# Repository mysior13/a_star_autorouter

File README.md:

Algorytm trasowania ścieżek na podstawie elementów rozmieszczonych na płytce oraz logicznych połączeń między tymi elementami, 
wyznacza możliwie najkrótsze ścieżki. 
Cechy programu:
-algorytm zalicza się do grupy algorytmów rastrowych,
-wyszukiwanie najkrótszej ścieżki przeprowadzane jest wykorzystaniem algorytmu A*,
-dane wejściowe (schemat płytki z rozłożonymi elementami oraz logicznymi połączeniami między nimi) wczytywane są z programu KiCad(program do projektowania płytek obwodów drukowanych)
-użytkownik posiada możliwość ustalenia maksymalnej liczby przelotek między warstwami, jakie dodać może algorytm,
-na wyjściu algorytm generuje obrazy z wyznaczonymi obszarami miedzi na każdej warstwie płytki drukowanej.

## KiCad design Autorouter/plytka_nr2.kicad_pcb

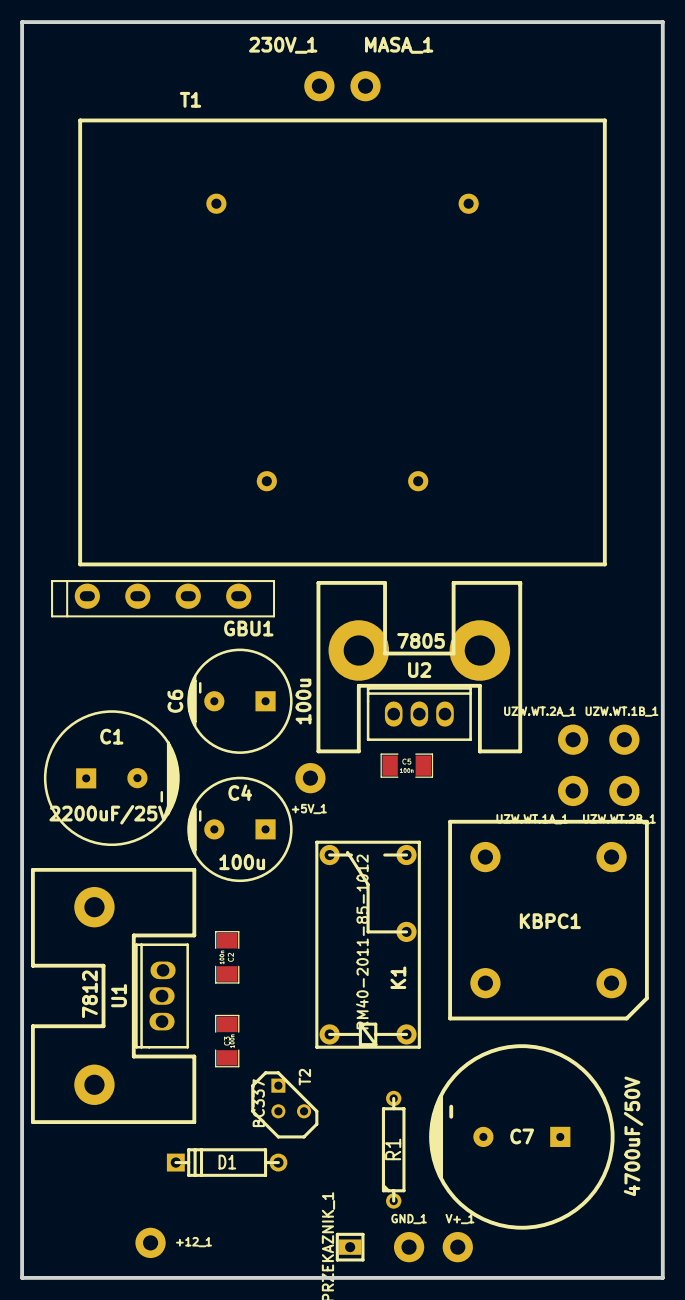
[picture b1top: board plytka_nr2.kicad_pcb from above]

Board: 2 copper layers, 63.5 x 124.5 mm, 27 parts (0 on the bottom side), 16 nets, no tracks yet.

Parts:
230V_1: CONN_1; 1pin_1.5mm
+5V_1, +12_1: CONN_1; 1pin_1.5mm
C1: 2200uF/25V; CP_13x21mm
C2, C3, C5: 100n; SM1206
C4, C6: 100u; CP_10x16mm
C7: 4700uF/50V; CP_18x37mm
D1: 1N5819; D4
GBU1: BRIDGE; GBU
GND_1: CONN_1; 1pin_1.5mm
K1: RM40-2011-85-1012; relay_PE
KBPC1: BRIDGE; KBPC10
MASA_1: CONN_1; 1pin_1.5mm
PRZEKAZNIK_1: CONN_1; pin_strip_1
R1: 4,7k; R4
T1: 12VA; Transformer_52x44
T2: BC337; TO92-EBC
U1: 7812; to220_radiator_25x50x16
U2: 7805; to220_radiator_20x40x16
UZW.WT.1A_1, UZW.WT.1B_1, UZW.WT.2A_1, UZW.WT.2B_1: CONN_1; 1pin_1.5mm
V+_1: CONN_1; 1pin_1.5mm

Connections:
/+5V: +5V_1.1, C5.1, C6.1, U2.3
/+12V: +12_1.1, C3.1, C4.1, D1.2, K1.1, U1.3, U2.1
/V+: C7.1, KBPC1.3, V+_1.1
GND: C1.2, C2.2, C3.2, C4.2, C5.2, C6.2, C7.2, GBU1.1, GND_1.1, KBPC1.1, T2.E, U1.2, U2.2
unnamed: KBPC1.2, UZW.WT.2B_1.1
unnamed: D1.1, K1.2, T2.C
unnamed: R1.2, T2.B
unnamed: PRZEKAZNIK_1.1, R1.1
unnamed: GBU1.4, T1.4
unnamed: GBU1.2, T1.3
unnamed: MASA_1.1, T1.2
unnamed: 230V_1.1, T1.1
unnamed: K1.11, KBPC1.4
unnamed: K1.14, UZW.WT.1B_1.1, UZW.WT.2A_1.1
unnamed: K1.12, UZW.WT.1A_1.1
unnamed: C1.1, C2.1, GBU1.3, U1.1

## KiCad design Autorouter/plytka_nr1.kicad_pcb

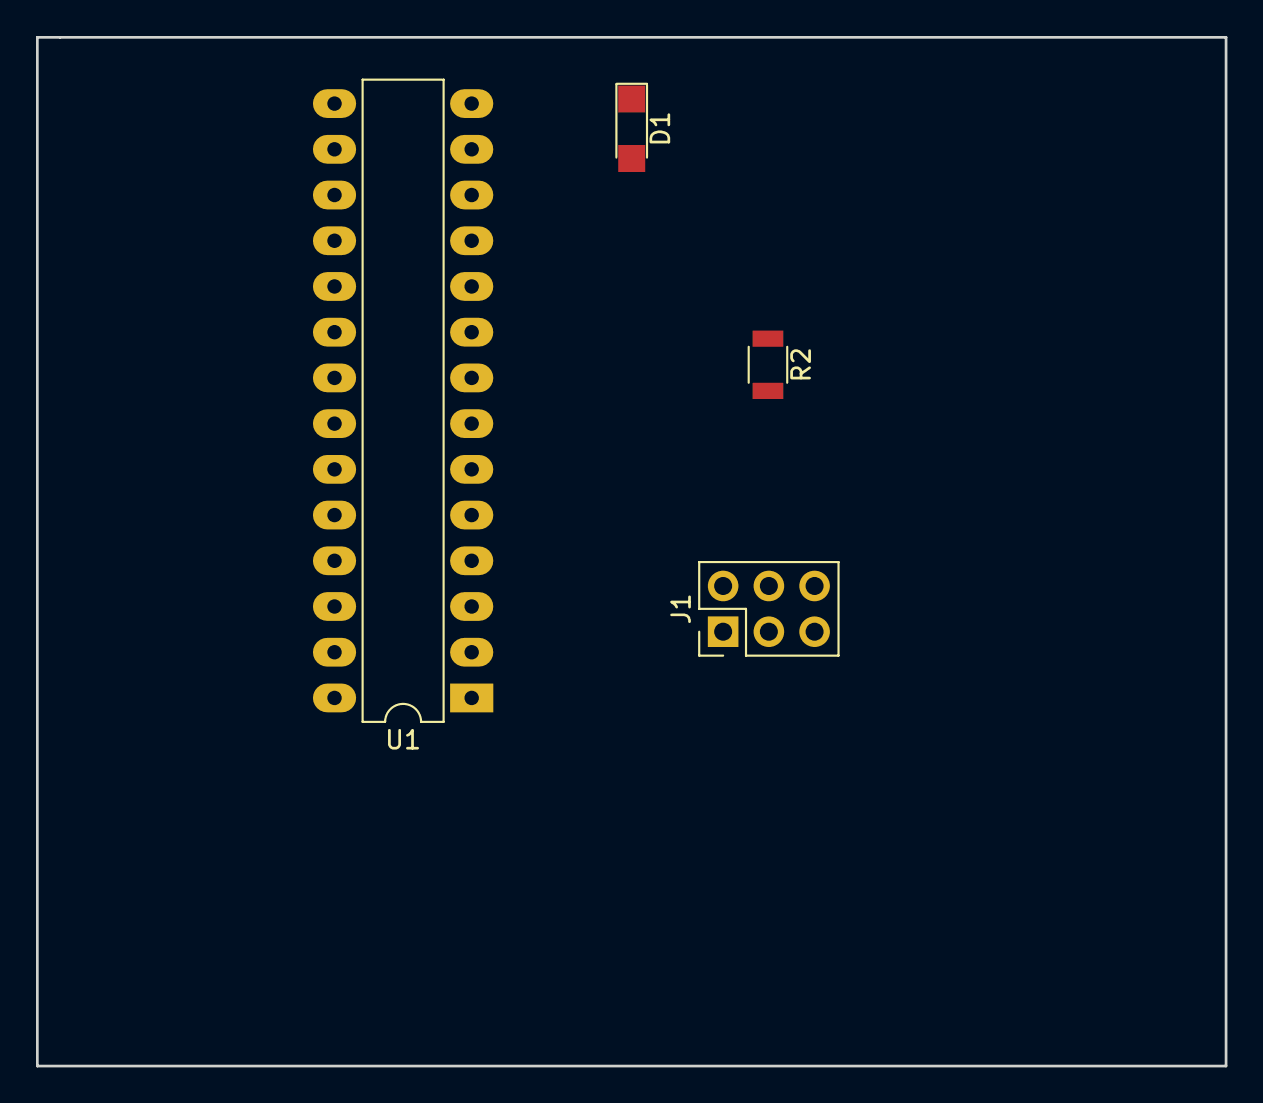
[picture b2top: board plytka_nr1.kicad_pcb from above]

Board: 2 copper layers, 66.0 x 57.2 mm, 5 parts (1 on the bottom side), 8 nets, no tracks yet.

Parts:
D1: LED; LED_1206
J1: Conn_02x03_Counter_Clockwise; Pin_Header_Straight_2x03_Pitch2.54mm
R1, R2: R; R_1206
U1: ATMEGA328P-PU; DIP-28_W7.62mm_LongPads

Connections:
GND: J1.4, R2.2, U1.8, U1.22
MISO: J1.1, U1.18
MOSI: J1.5, U1.17
unnamed: D1.1, R2.1
unnamed: D1.2, U1.2
RST: J1.3, R1.2, U1.1
SCK: J1.2, U1.19
VCC: J1.6, R1.1, U1.7

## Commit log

2018-11-13 Readme file creation
